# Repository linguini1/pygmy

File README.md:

# Pygmy

This project is a rocket flight computer design for my TRA L1 certification flight. The name is a play on the fact that
it's designed to be small and also runs on a Pi (Py) chip. Yes, that means you can program it with MicroPython (Py).

The Pygmy was designed with the [Apache NuttX RTOS][nuttx] in mind (you can find the board support for it
[here][pygmy-nx]), but it is also possible to program it using the Pico C SDK or MicroPython (or really, whatever else
you can flash on an RP2040).

<p align="center">
    
    <br/>
    Pygmy Rev B
</p>

<p align="center">
    
    <br/>
    The prototype board Pygmy Rev B with its ground station sibling, PygmyGS.
</p>

The flight computer also has a sibling ground station receiver, the PygmyGS. This board allows you to receive telemetry
from the ground and can interface with consumer hardware like a laptop through its USB-C serial interface.

<p align="center">
    
    <br/>
    The manufactured PygmyGS Rev A
</p>

<p align="center">
    
    <br/>
    Handheld for scale
</p>

<p align="center">
    
    <br/>
    The ECAD render of the PygmyGS Rev A
</p>

Here is the Pygmy within my L1 rocket:

## Motivation

I am a computer systems engineer who has designed avionics for my university's rocketry team for several years. I like
the challenge of designing, building and programming embedded systems for unique environments, like the inside of a
rocket. Although my L1 flight won't have the same challenges as my university's rockets (which fly up to 30k feet and
have hit Mach 1.89), it will still have challenges unique to rocketry like high vibration and lots of different forces,
arming requirements and logging speed requirements. Most differently, this flight computer is entirely my own project to
experiment with as I please!

My L1, as far as I'm concerned, is to be a relatively standard L1 rocket build (not a kit, still my own) outside of this
flight computer. That way I can get my cert while having a rocket which meets my primary goal: being a vessel for my
flight computer.

This flight computer, once flight tested in an L1, should in theory be capable up to L3 flights as a data logger.
Deployment control may be added in later revisions as I attempt my L2 certification with electronics, but that will be
much later.

## Usage

To learn how to use the Pygmy, please check the manual under the `docs/` sub-directory. This manual contains both the
user guide for operation and a detailed developer guide.

Both guides are currently under construction.

## Other Goodies

Along with the Pygmy and PygmyGS E-CAD design files _and_ free,
[open-source software](https://github.com/linguini1/pygmy-nx), there is additionally parametric CAD enclosure designs
included in this repository.

The PygmyGS case can be found under [`ground-station/enclosure`](./ground-station/enclosure), along with an assembly
file so you can see the PygmyGS mounted inside it with all the fasteners.

<p align="center">
    
    <br/>
    PygmyGS hinged enclosure
</p>

A sample avionics bay for the Pygmy flight computer can be found under
[`flight-computer/enclosure`](./flight-computer/enclosure), along with an assembly file so you can see the Pygmy mounted
in the bay with a battery and arming switch. This design is also fully parametric so you can modify it to the body tube
diameter of your rocket, different battery size, etc. This design is largely based off of the configuration I flew in my
L1 certification flight, so feel free to fully change it depending on your constraints and desires! It is by no way the
recommended configuration for the Pygmy, just one possible design.

<p align="center">
    
    <br/>
    Pygmy sample avionics bay
</p>

[pygmy-nx]: https://github.com/linguini1/pygmy-nx
[nuttx]: https://nuttx.apache.org/

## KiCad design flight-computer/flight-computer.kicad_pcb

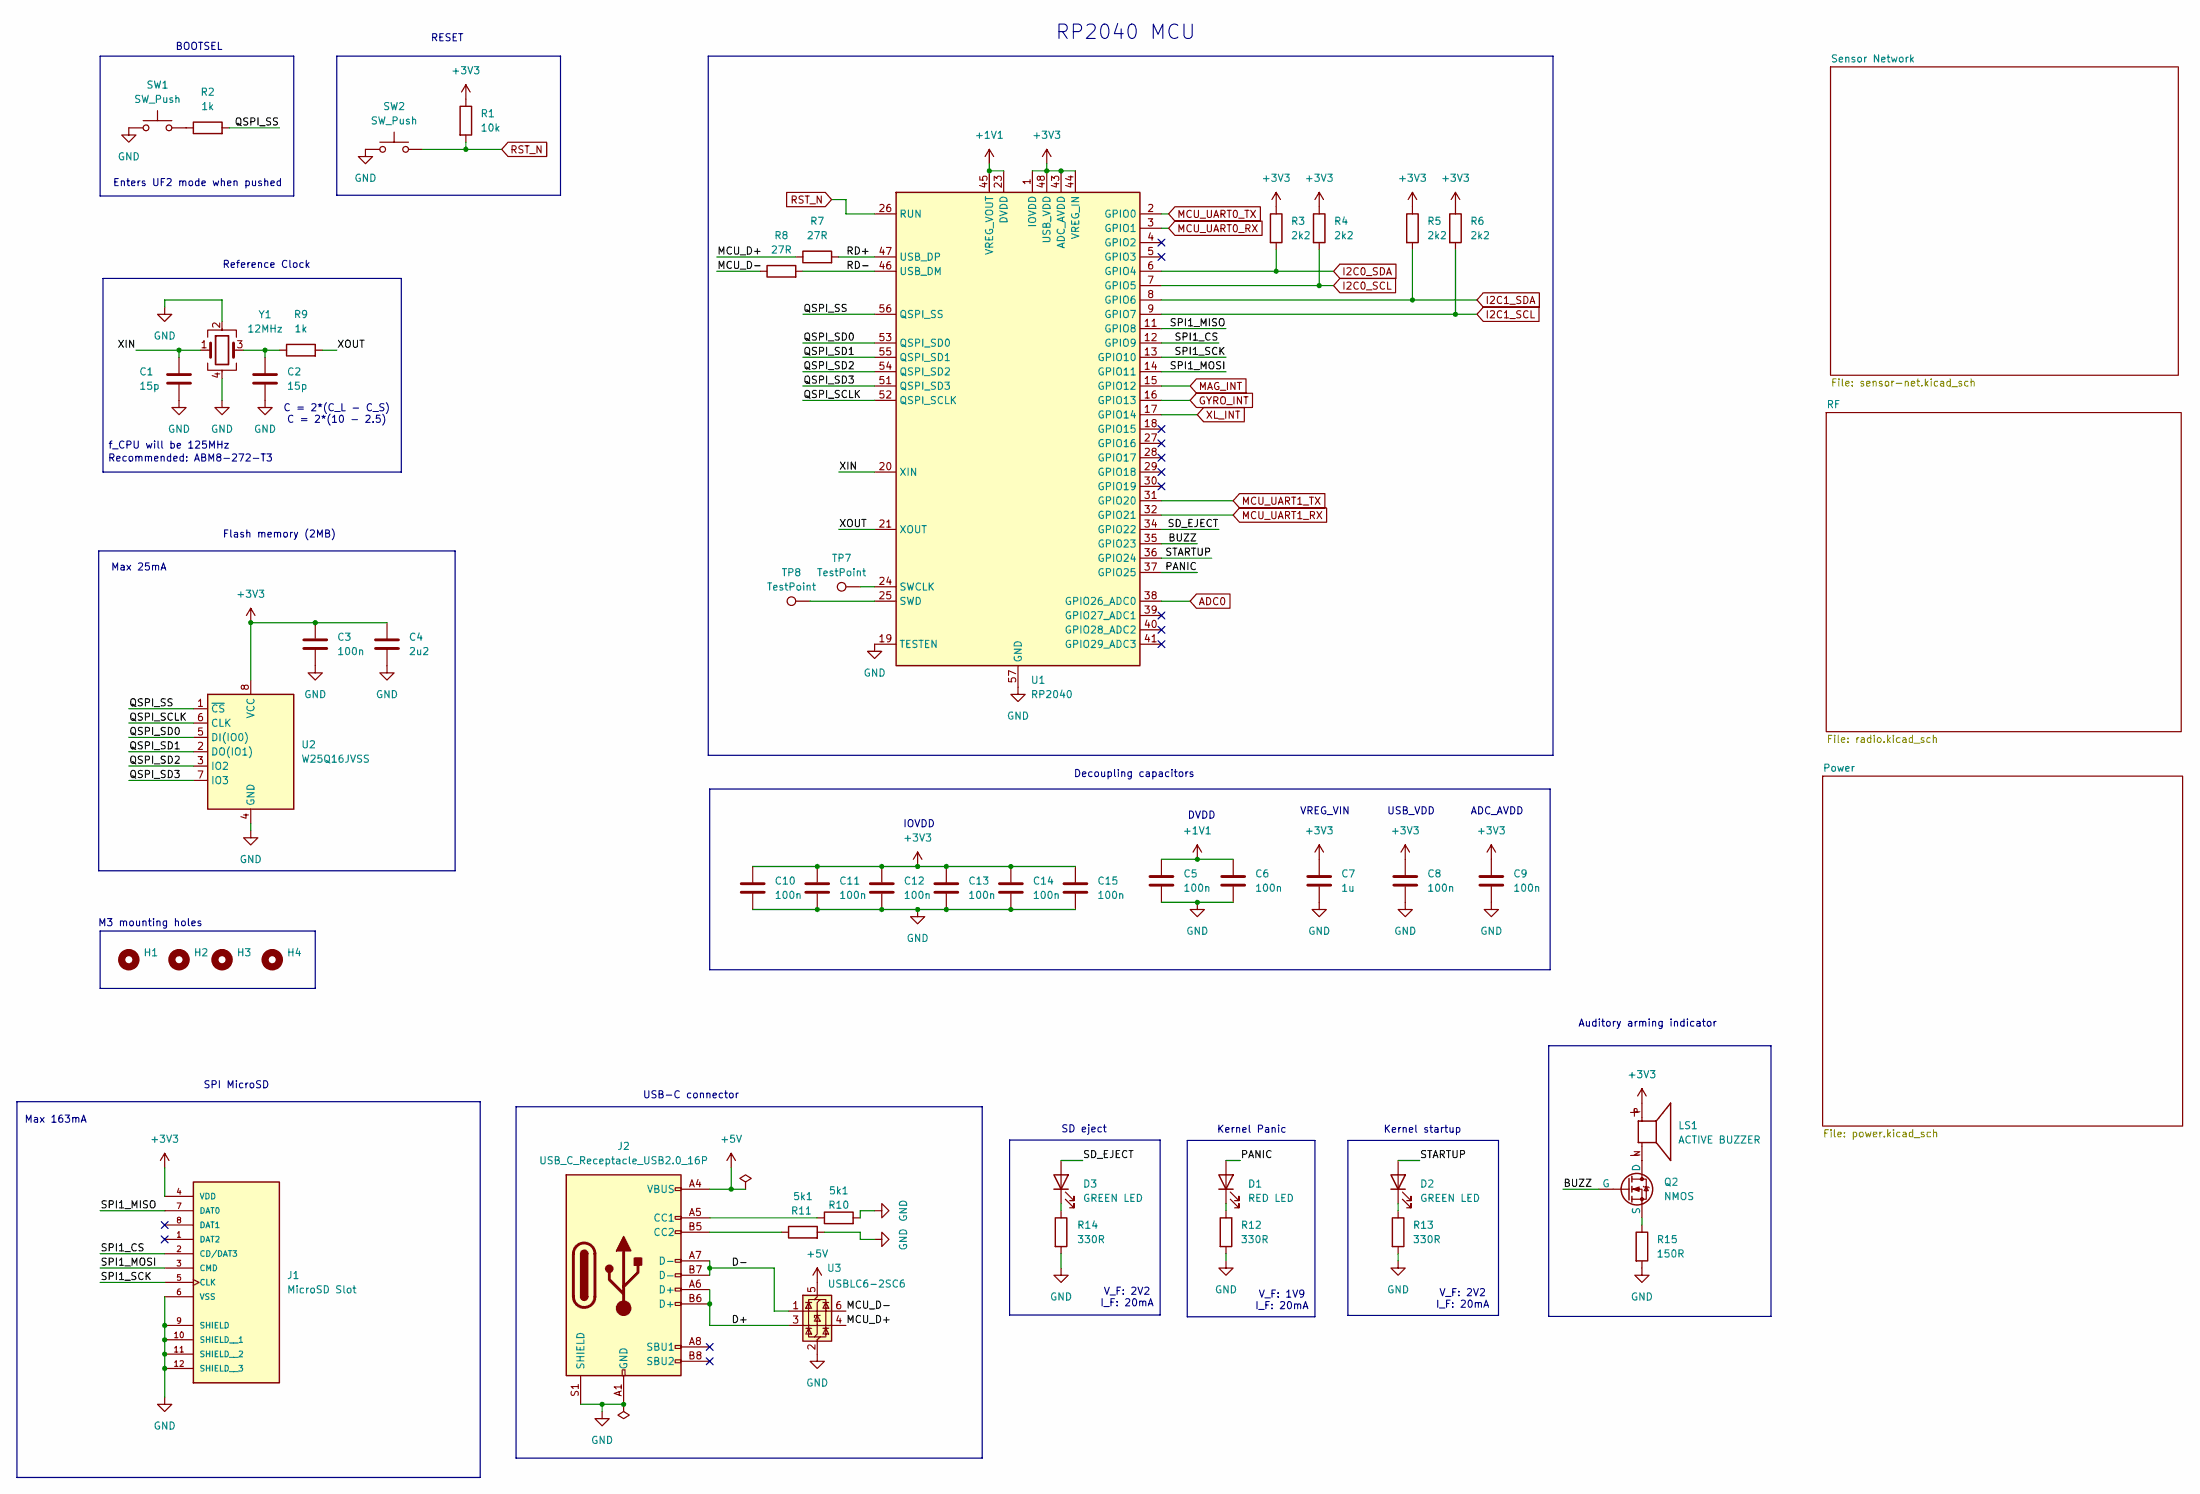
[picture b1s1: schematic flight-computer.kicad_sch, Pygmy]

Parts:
C1, C2: 15p; C_0402_1005Metric
C3, C5, C6, C8, C9, C10, C11, C12, C13, C14, C15: 100n; C_0402_1005Metric
C4: 2u2; C_0603_1608Metric
C7: 1u; C_0603_1608Metric
D1: RED LED; LED_0805_2012Metric
D2, D3: GREEN LED; LED_0805_2012Metric
H1, H2, H3, H4: MountingHole; MountingHole_3.2mm_M3
J1: MicroSD Slot; GCT_MEM2067-02-180-00-A_REVB
J2: USB_C_Receptacle_USB2.0_16P; USB_C_Receptacle_GCT_USB4105-xx-A_16P_TopMnt_Horizontal
LS1: ACTIVE BUZZER; XDCR_AI-1223-TWT-3V-2-R; PARTREV 3/18/2020
Q2: NMOS; SOT-23-3
R1: 10k; R_0402_1005Metric
R2, R9: 1k; R_0402_1005Metric
R3, R4, R5, R6: 2k2; R_0402_1005Metric
R7, R8: 27R; R_0402_1005Metric
R10, R11: 5k1; R_0402_1005Metric
R12, R13, R14: 330R; R_0402_1005Metric
R15: 150R; R_0402_1005Metric
SW1: SW_Push; SW_PUSH_6mm_H5mm
SW2: SW_Push; SolderJumper-2_P1.3mm_Open_TrianglePad1.0x1.5mm
TP7, TP8: TestPoint; TestPoint_Pad_D1.5mm
U1: RP2040; QFN-56-1EP_7x7mm_P0.4mm_EP3.2x3.2mm
U2: W25Q16JVSS; SOIC-8_5.23x5.23mm_P1.27mm
U3: USBLC6-2SC6; SOT-23-6
Y1: 12MHz; Crystal_SMD_3225-4Pin_3.2x2.5mm

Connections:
+1V1: C5.1, C6.1, U1.23 (DVDD), U1.45 (VREG_VOUT), U1.50 (DVDD)
+3V3: C3.1, C4.1, C7.1, C8.1, C9.1, C10.1, C11.1, C12.1, C13.1, C14.1, C15.1, J1.4 (VDD), LS1.P, R1.1, R3.1, R4.1, R5.1, R6.1, U1.1 (IOVDD), U1.10 (IOVDD), U1.22 (IOVDD), U1.33 (IOVDD), U1.42 (IOVDD), U1.43 (ADC_AVDD), U1.44 (VREG_IN), U1.48 (USB_VDD), U1.49 (IOVDD), U2.8 (VCC); also elsewhere on the board
+5V: J2.A4 (VBUS), J2.A9 (VBUS), J2.B4 (VBUS), J2.B9 (VBUS), U3.5 (VBUS); also elsewhere on the board
/BUZZ: Q2.1 (G), U1.35 (GPIO23)
/D+: J2.A6 (D+), J2.B6 (D+), U3.3 (I/O2)
/D-: J2.A7 (D-), J2.B7 (D-), U3.1 (I/O1)
/MCU_D+: R7.1, U3.4 (I/O2)
/MCU_D-: R8.1, U3.6 (I/O1)
/PANIC: D1.2 (A), U1.37 (GPIO25)
/QSPI_SCLK: U1.52 (QSPI_SCLK), U2.6 (CLK)
/QSPI_SD0: U1.53 (QSPI_SD0), U2.5 (DI(IO0))
/QSPI_SD1: U1.55 (QSPI_SD1), U2.2 (DO(IO1))
/QSPI_SD2: U1.54 (QSPI_SD2), U2.3 (IO2)
/QSPI_SD3: U1.51 (QSPI_SD3), U2.7 (IO3)
/QSPI_SS: R2.2, U1.56 (QSPI_SS), U2.1 (~CS)
/RD+: R7.2, U1.47 (USB_DP)
/RD-: R8.2, U1.46 (USB_DM)
/SD_EJECT: D3.2 (A), U1.34 (GPIO22)
/SPI1_CS: J1.2 (CD/DAT3), U1.12 (GPIO9)
/SPI1_MISO: J1.7 (DAT0), U1.11 (GPIO8)
/SPI1_MOSI: J1.3 (CMD), U1.14 (GPIO11)
/SPI1_SCK: J1.5 (CLK), U1.13 (GPIO10)
/STARTUP: D2.2 (A), U1.36 (GPIO24)
/XIN: C1.1, U1.20 (XIN), Y1.1
/XOUT: R9.2, U1.21 (XOUT)
ADC0: U1.38 (GPIO26_ADC0); also elsewhere on the board
GND: C1.2, C2.2, C3.2, C4.2, C5.2, C6.2, C7.2, C8.2, C9.2, C10.2, C11.2, C12.2, C13.2, C14.2, C15.2, J1.6 (VSS), J1.9 (SHIELD), J1.10 (SHIELD__1), J1.11 (SHIELD__2), J1.12 (SHIELD__3), J2.A1 (GND), J2.A12 (GND), J2.B1 (GND), J2.B12 (GND), J2.S1 (SHIELD), R10.2, R11.2, R12.2, R13.2, R14.2, R15.2, SW1.1, SW2.1, U1.19 (TESTEN), U1.57 (GND), U2.4 (GND), U3.2 (GND), Y1.2, Y1.4; also elsewhere on the board
GYRO_INT: U1.16 (GPIO13); also elsewhere on the board
I2C0_SCL: R4.2, U1.7 (GPIO5); also elsewhere on the board
I2C0_SDA: R3.2, U1.6 (GPIO4); also elsewhere on the board
I2C1_SCL: R6.2, U1.9 (GPIO7); also elsewhere on the board
I2C1_SDA: R5.2, U1.8 (GPIO6); also elsewhere on the board
MAG_INT: U1.15 (GPIO12); also elsewhere on the board
MCU_UART0_RX: U1.3 (GPIO1); also elsewhere on the board
MCU_UART0_TX: U1.2 (GPIO0); also elsewhere on the board
MCU_UART1_RX: U1.32 (GPIO21); also elsewhere on the board
MCU_UART1_TX: U1.31 (GPIO20); also elsewhere on the board
unnamed: C2.1, R9.1, Y1.3
unnamed: D1.1 (K), R12.1
unnamed: D2.1 (K), R13.1
unnamed: D3.1 (K), R14.1
unnamed: J2.A5 (CC1), R10.1
unnamed: J2.B5 (CC2), R11.1
unnamed: LS1.N, Q2.3 (D)
unnamed: Q2.2 (S), R15.1
unnamed: R2.1, SW1.2
unnamed 54: TP7.1, U1.24 (SWCLK); also elsewhere on the board
unnamed 55: TP8.1, U1.25 (SWD); also elsewhere on the board
RST_N: R1.2, SW2.2, U1.26 (RUN); also elsewhere on the board
XL_INT: U1.17 (GPIO14); also elsewhere on the board

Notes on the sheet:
Auditory arming indicator
RP2040 MCU
C = 2*(C_L - C_S) C = 2*(10 - 2.5)
Kernel Panic
Kernel startup
V_F: 2V2 I_F: 20mA
VREG_VIN
USB_VDD
Recommended: ABM8-272-T3
Max 163mA
DVDD
M3 mounting holes
IOVDD
SPI MicroSD
USB-C connector
f_CPU will be 125MHz
V_F: 1V9 I_F: 20mA
Decoupling capacitors
BOOTSEL
Reference Clock
ADC_AVDD
RESET
Flash memory (2MB)
Max 25mA
Enters UF2 mode when pushed
SD eject

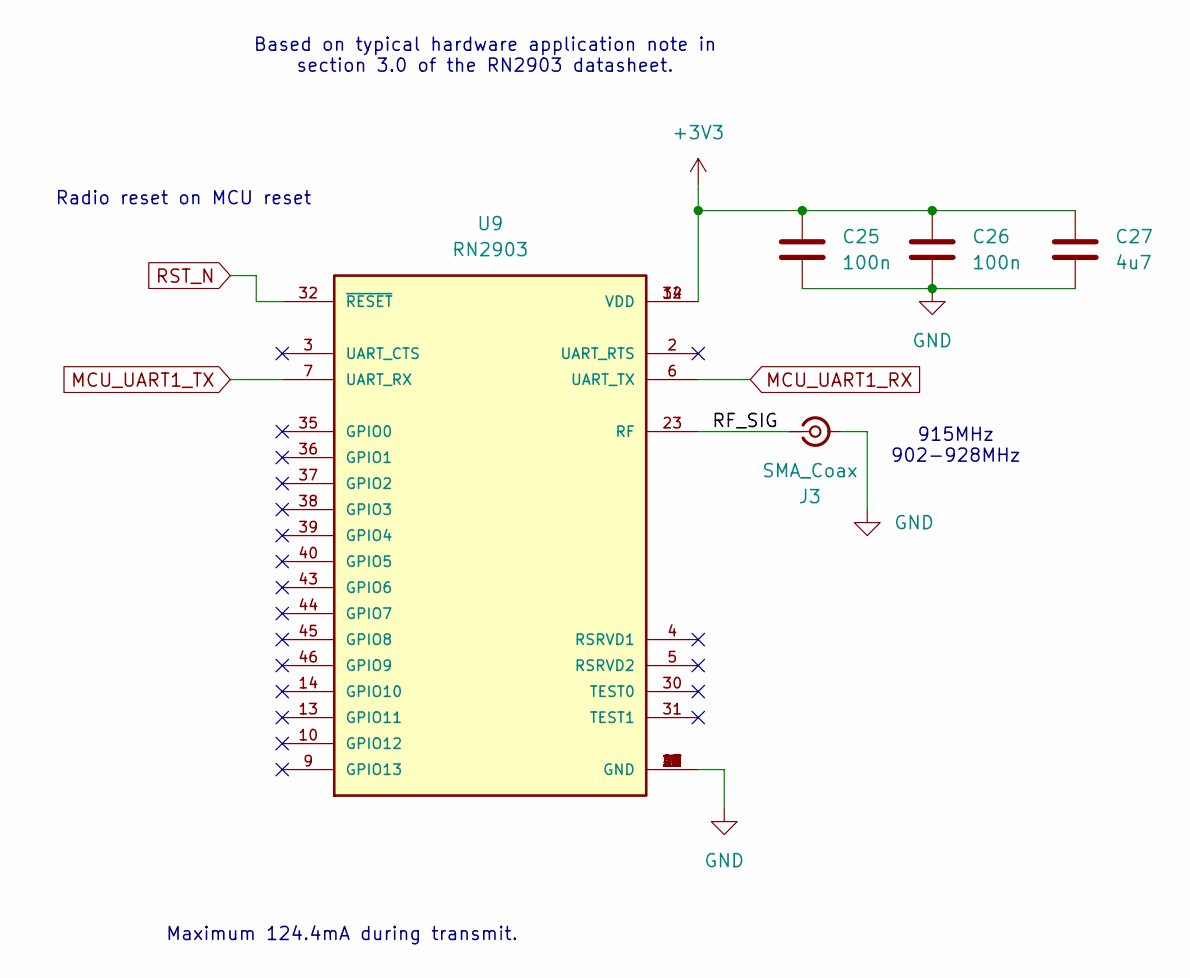
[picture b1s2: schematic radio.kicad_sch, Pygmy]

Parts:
C25, C26: 100n; C_0402_1005Metric
C27: 4u7; C_0603_1608Metric
J3: SMA_Coax; SMA_Molex_73251-1153_EdgeMount_Horizontal
U9: RN2903

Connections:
+3V3: C25.1, C26.1, C27.1, U9.12 (VDD), U9.34 (VDD); also elsewhere on the board
/RF/RF_SIG: J3.1 (In), U9.23 (RF)
GND: C25.2, C26.2, C27.2, J3.2 (Ext), U9.1 (GND), U9.8 (GND), U9.11 (GND), U9.20 (GND), U9.21 (GND), U9.22 (GND), U9.24 (GND), U9.26 (GND), U9.27 (GND), U9.28 (GND), U9.33 (GND), U9.41 (GND), U9.47 (GND); also elsewhere on the board
MCU_UART1_RX: U9.6 (UART_TX); also elsewhere on the board
MCU_UART1_TX: U9.7 (UART_RX); also elsewhere on the board
RST_N: U9.32 (~RESET); also elsewhere on the board

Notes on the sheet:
915MHz 902-928MHz
Radio reset on MCU reset
Maximum 124.4mA during transmit.
Based on typical hardware application note in section 3.0 of the RN2903 datasheet.

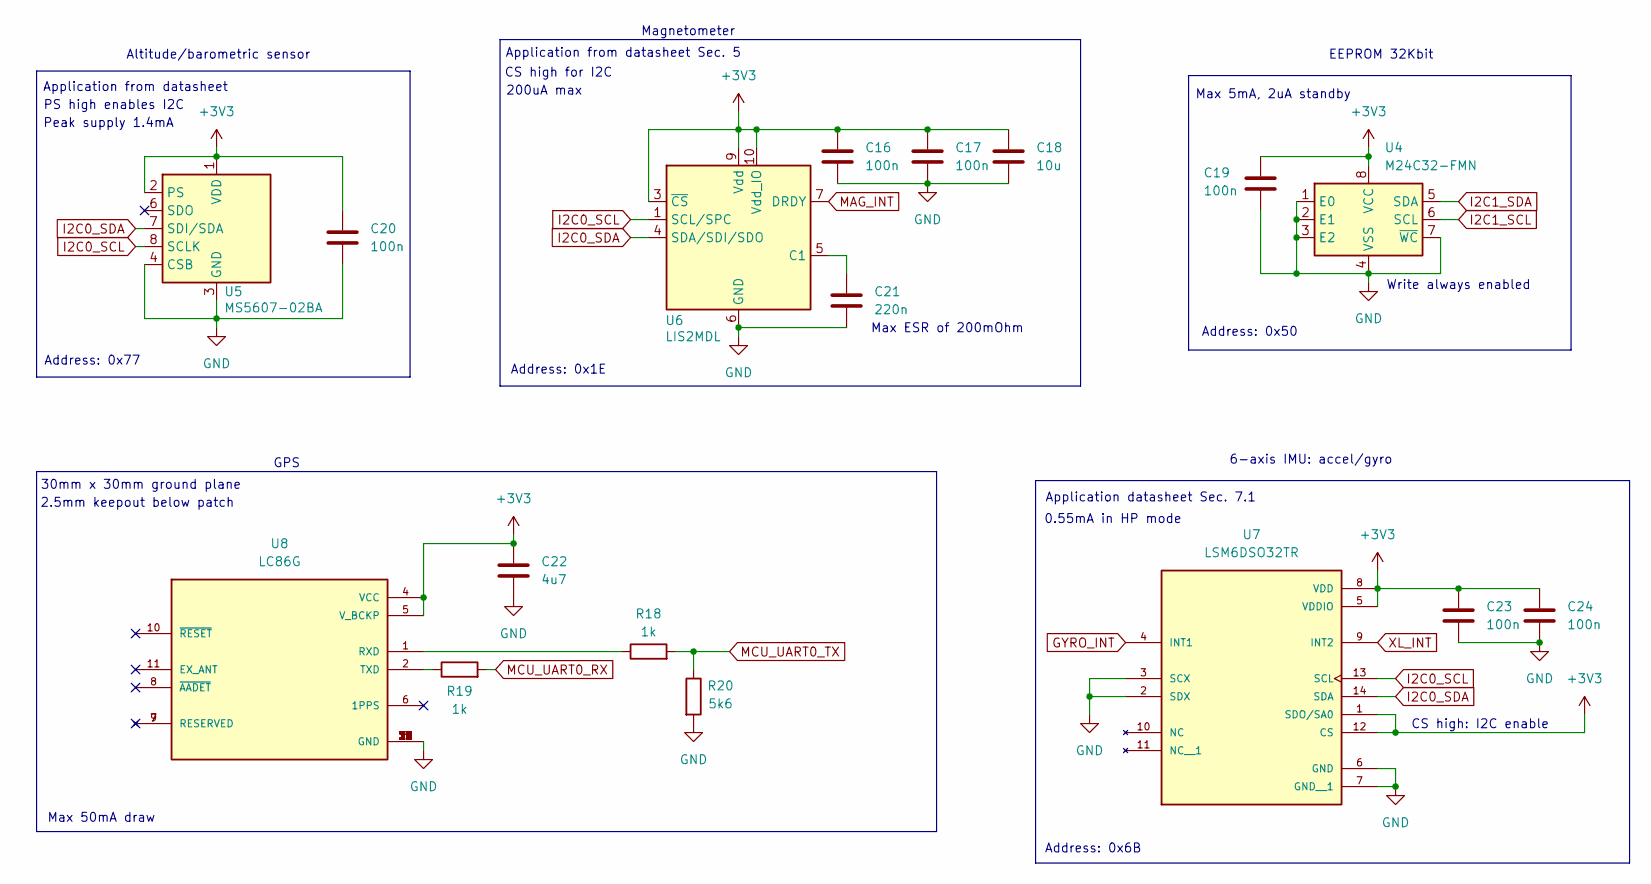
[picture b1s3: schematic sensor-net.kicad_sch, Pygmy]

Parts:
C16, C17, C19, C20, C23, C24: 100n; C_0402_1005Metric
C18: 10u; C_0603_1608Metric
C21: 220n; C_0603_1608Metric
C22: 4u7; C_0603_1608Metric
R18, R19: 1k; R_0402_1005Metric
R20: 5k6; R_0402_1005Metric
U4: M24C32-FMN; SOIC-8_3.9x4.9mm_P1.27mm
U5: MS5607-02BA; LGA-8_3x5mm_P1.25mm
U6: LIS2MDL; LGA-12_2x2mm_P0.5mm
U7: LSM6DSO32TR; XDCR_LSM6DSO32TR
U8: LC86G; XCVR_LC86G

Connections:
+3V3: C16.1, C17.1, C18.1, C19.1, C20.1, C22.1, C23.1, C24.1, U4.8 (VCC), U5.1 (VDD), U5.2 (PS), U6.3 (~CS), U6.9 (Vdd), U6.10 (Vdd_IO), U7.1 (SDO/SA0), U7.5 (VDDIO), U7.8 (VDD), U7.12 (CS), U8.4 (VCC), U8.5 (V_BCKP); also elsewhere on the board
GND: C16.2, C17.2, C18.2, C19.2, C20.2, C21.2, C22.2, C23.2, C24.2, R20.2, U4.1 (E0), U4.2 (E1), U4.3 (E2), U4.4 (VSS), U4.7 (~WC), U5.3 (GND), U5.4 (CSB), U5.5 (CSB), U6.6 (GND), U6.8 (GND), U7.2 (SDX), U7.3 (SCX), U7.6 (GND), U7.7 (GND__1), U8.3 (GND), U8.12 (GND), U8.13 (GND), U8.14 (GND), U8.15 (GND), U8.16 (GND), U8.17 (GND), U8.18 (GND), U8.19 (GND), U8.20 (GND), U8.21 (GND), U8.22 (GND), U8.23 (GND), U8.24 (GND), U8.25 (GND), U8.26 (GND), U8.27 (GND), U8.28 (GND), U8.29 (GND), U8.30 (GND), U8.31 (GND), U8.32 (GND), U8.33 (GND), U8.34 (GND), U8.35 (GND), U8.36 (GND); also elsewhere on the board
GYRO_INT: U7.4 (INT1); also elsewhere on the board
I2C0_SCL: U5.8 (SCLK), U6.1 (SCL/SPC), U7.13 (SCL); also elsewhere on the board
I2C0_SDA: U5.7 (SDI/SDA), U6.4 (SDA/SDI/SDO), U7.14 (SDA); also elsewhere on the board
I2C1_SCL: U4.6 (SCL); also elsewhere on the board
I2C1_SDA: U4.5 (SDA); also elsewhere on the board
MAG_INT: U6.7 (DRDY); also elsewhere on the board
MCU_UART0_RX: R19.2; also elsewhere on the board
MCU_UART0_TX: R18.2, R20.1; also elsewhere on the board
unnamed: C21.1, U6.5 (C1)
unnamed: R18.1, U8.1 (RXD)
unnamed: R19.1, U8.2 (TXD)
XL_INT: U7.9 (INT2); also elsewhere on the board

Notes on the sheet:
Application datasheet Sec. 7.1
CS high for I2C
Address: 0x50
Address: 0x6B
Application from datasheet Sec. 5
Address: 0x77
30mm x 30mm ground plane
Altitude/barometric sensor
Max 5mA, 2uA standby
GPS
6-axis IMU: accel/gyro
200uA max
Magnetometer
Address: 0x1E
EEPROM 32Kbit
CS high: I2C enable
Write always enabled
PS high enables I2C
Application from datasheet
Peak supply 1.4mA
2.5mm keepout below patch
Max 50mA draw
0.55mA in HP mode
Max ESR of 200mOhm

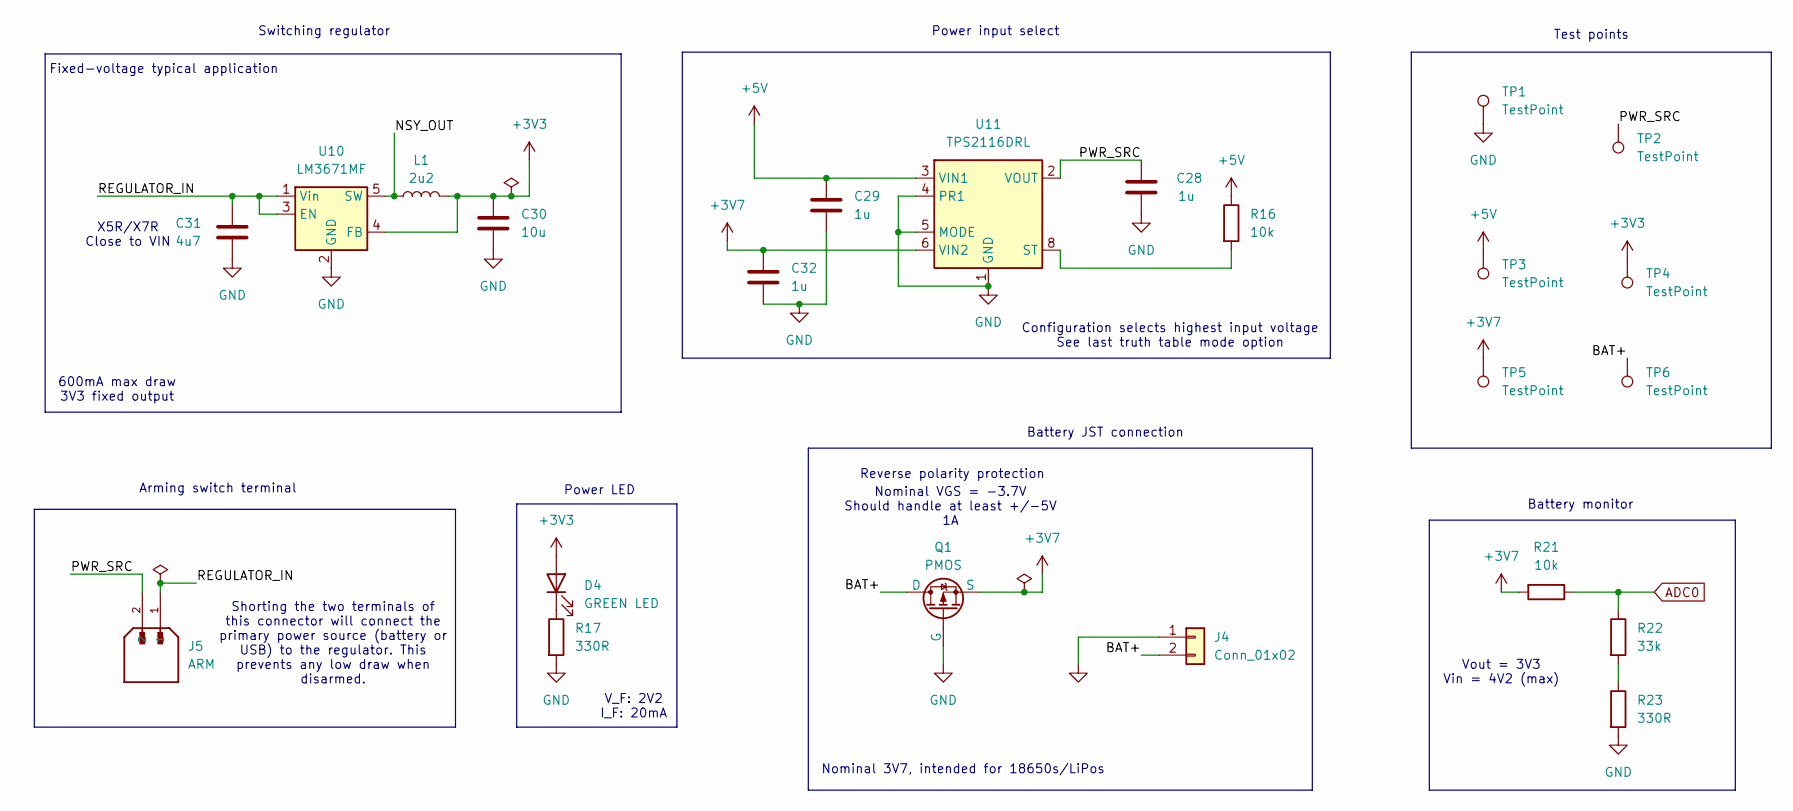
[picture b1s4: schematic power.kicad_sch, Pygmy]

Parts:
C28, C29, C32: 1u; C_0603_1608Metric
C30: 10u; C_0603_1608Metric
C31: 4u7; C_0603_1608Metric
D4: GREEN LED; LED_0805_2012Metric
J4: Conn_01x02; JST_PH_S2B-PH-K_1x02_P2.00mm_Horizontal
J5: ARM; TerminalBlock_Phoenix_MPT-0,5-2-2.54_1x02_P2.54mm_Horizontal; PARTREV A2
L1: 2u2; LPO3310222MLC
Q1: PMOS; SOT-23-3
R16, R21: 10k; R_0402_1005Metric
R17, R23: 330R; R_0402_1005Metric
R22: 33k; R_0402_1005Metric
TP1, TP2, TP4, TP5, TP6: TestPoint; TestPoint_Pad_D1.5mm
TP3: TestPoint; TestPoint_Pad_D1.0mm
U10: LM3671MF; TSOT-23-5
U11: TPS2116DRL; SOT-583-8

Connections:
+3V3: C30.1, D4.2 (A), L1.2, TP4.1, U10.4 (FB); also elsewhere on the board
+3V7: C32.1, Q1.2 (S), R21.2, TP5.1, U11.6 (VIN2); also elsewhere on the board
+5V: C29.1, R16.1, TP3.1, U11.3 (VIN1); also elsewhere on the board
/Power/BAT+: J4.2, Q1.3 (D), TP6.1; also elsewhere on the board
/Power/NSY_OUT: L1.1, U10.5 (SW)
/Power/PWR_SRC: C28.1, J5.2, TP2.1, U11.2 (VOUT), U11.7 (VOUT); also elsewhere on the board
/Power/REGULATOR_IN: C31.1, J5.1, U10.1 (Vin), U10.3 (EN)
ADC0: R21.1, R22.1; also elsewhere on the board
GND: C28.2, C29.2, C30.2, C31.2, C32.2, J4.1, Q1.1 (G), R17.2, R23.2, TP1.1, U10.2 (GND), U11.1 (GND), U11.4 (PR1), U11.5 (MODE); also elsewhere on the board
unnamed: D4.1 (K), R17.1
unnamed: R22.2, R23.1
unnamed: R16.2, U11.8 (ST)

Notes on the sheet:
Arming switch terminal
V_F: 2V2 I_F: 20mA
Switching regulator
Nominal VGS = -3.7V Should handle at least +/-5V 1A
Configuration selects highest input voltage See last truth table mode option
Vout = 3V3 Vin = 4V2 (max)
Shorting the two terminals of this connector will connect the primary power source (battery or USB) to the regulator. This prevents any low draw when disarmed.
600mA max draw 3V3 fixed output
Nominal 3V7, intended for 18650s/LiPos
Fixed-voltage typical application
Test points
Power input select
X5R/X7R Close to VIN
Battery JST connection
Power LED
Reverse polarity protection
Battery monitor

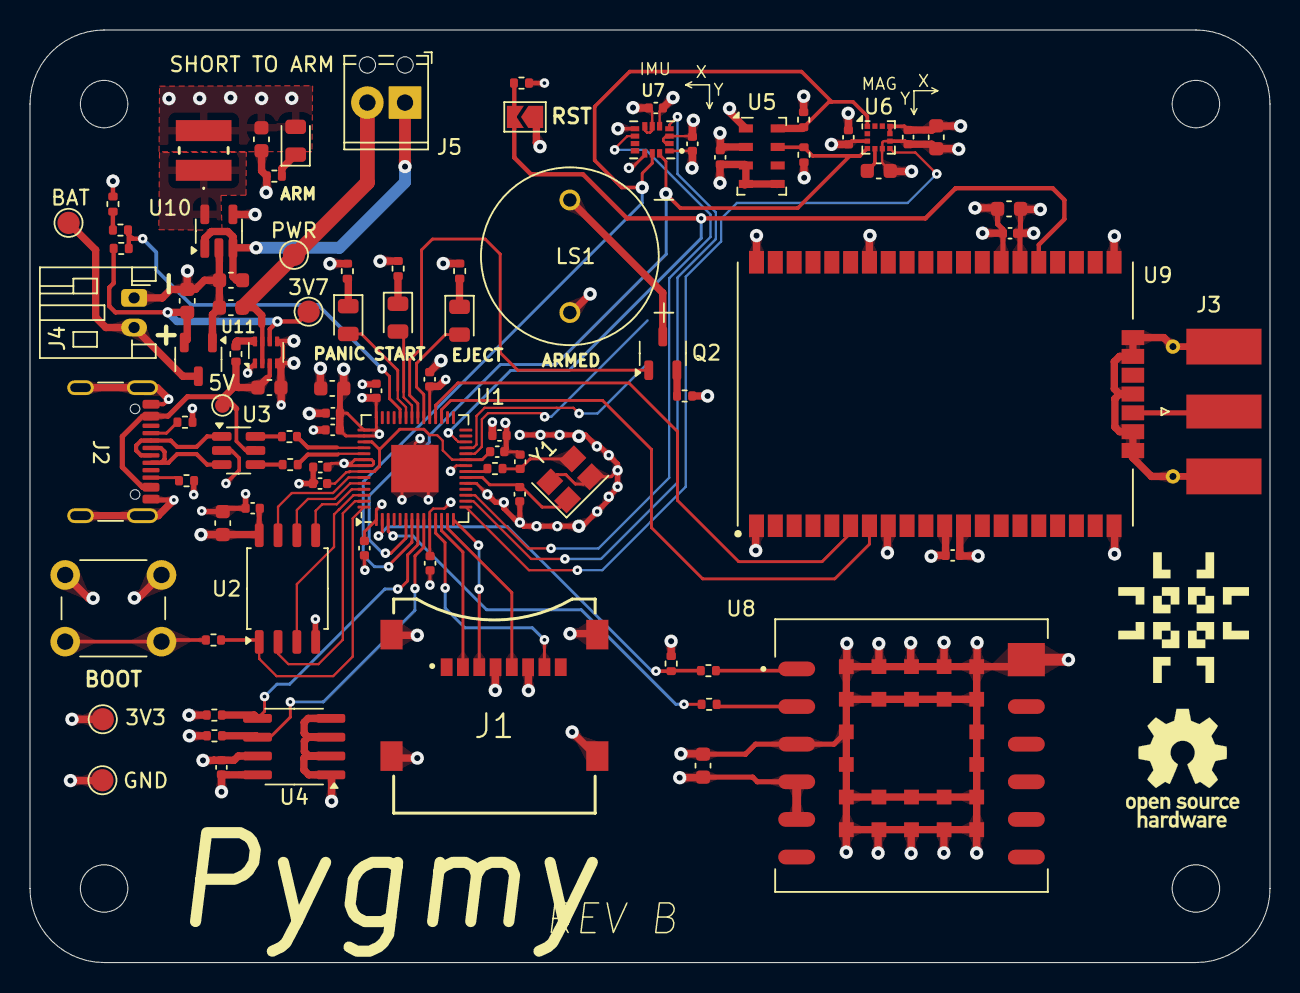
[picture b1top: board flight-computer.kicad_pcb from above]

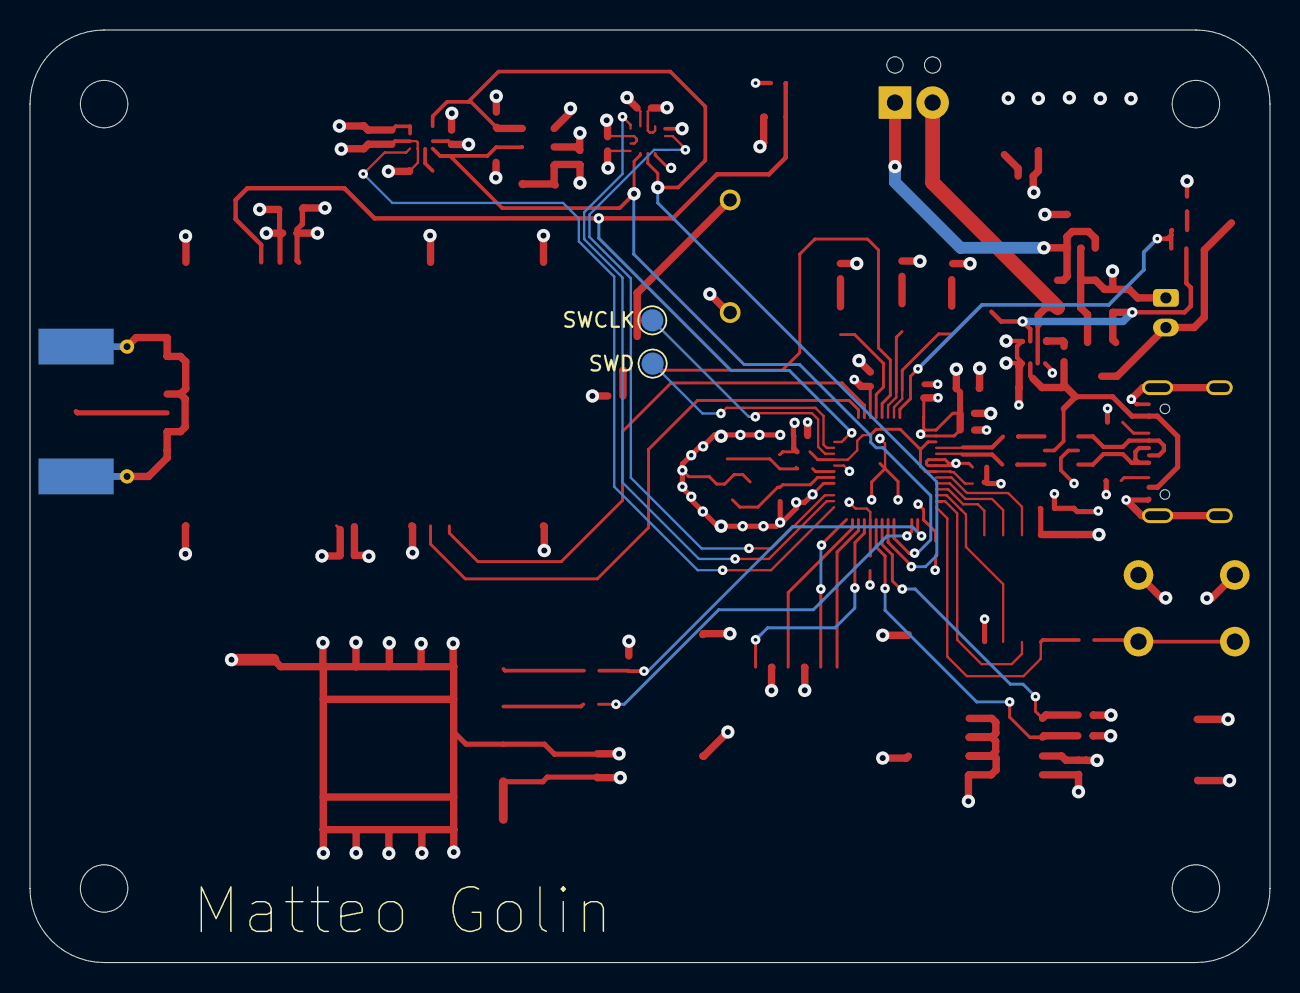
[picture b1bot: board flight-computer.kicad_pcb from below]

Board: 4 copper layers, 83.7 x 62.9 mm, 94 parts (2 on the bottom side), 62 nets.

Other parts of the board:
3V3, 3V7: TestPoint; TestPoint_Pad_D1.5mm
5V: TestPoint; TestPoint_Pad_D1.0mm
BAT: TestPoint; TestPoint_Pad_D1.5mm
GND: TestPoint; TestPoint_Pad_D1.5mm
PWR: TestPoint; TestPoint_Pad_D1.5mm
SWCLK: TestPoint; TestPoint_Pad_D1.5mm
SWD: TestPoint; TestPoint_Pad_D1.5mm

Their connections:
+3V3: 3V3.1; also elsewhere on the board
+3V7: 3V7.1; also elsewhere on the board
+5V: 5V.1; also elsewhere on the board
/Power/BAT+: BAT.1; also elsewhere on the board
/Power/PWR_SRC: PWR.1; also elsewhere on the board
GND: GND.1; also elsewhere on the board
unnamed 54: SWCLK.1; also elsewhere on the board
unnamed 55: SWD.1; also elsewhere on the board

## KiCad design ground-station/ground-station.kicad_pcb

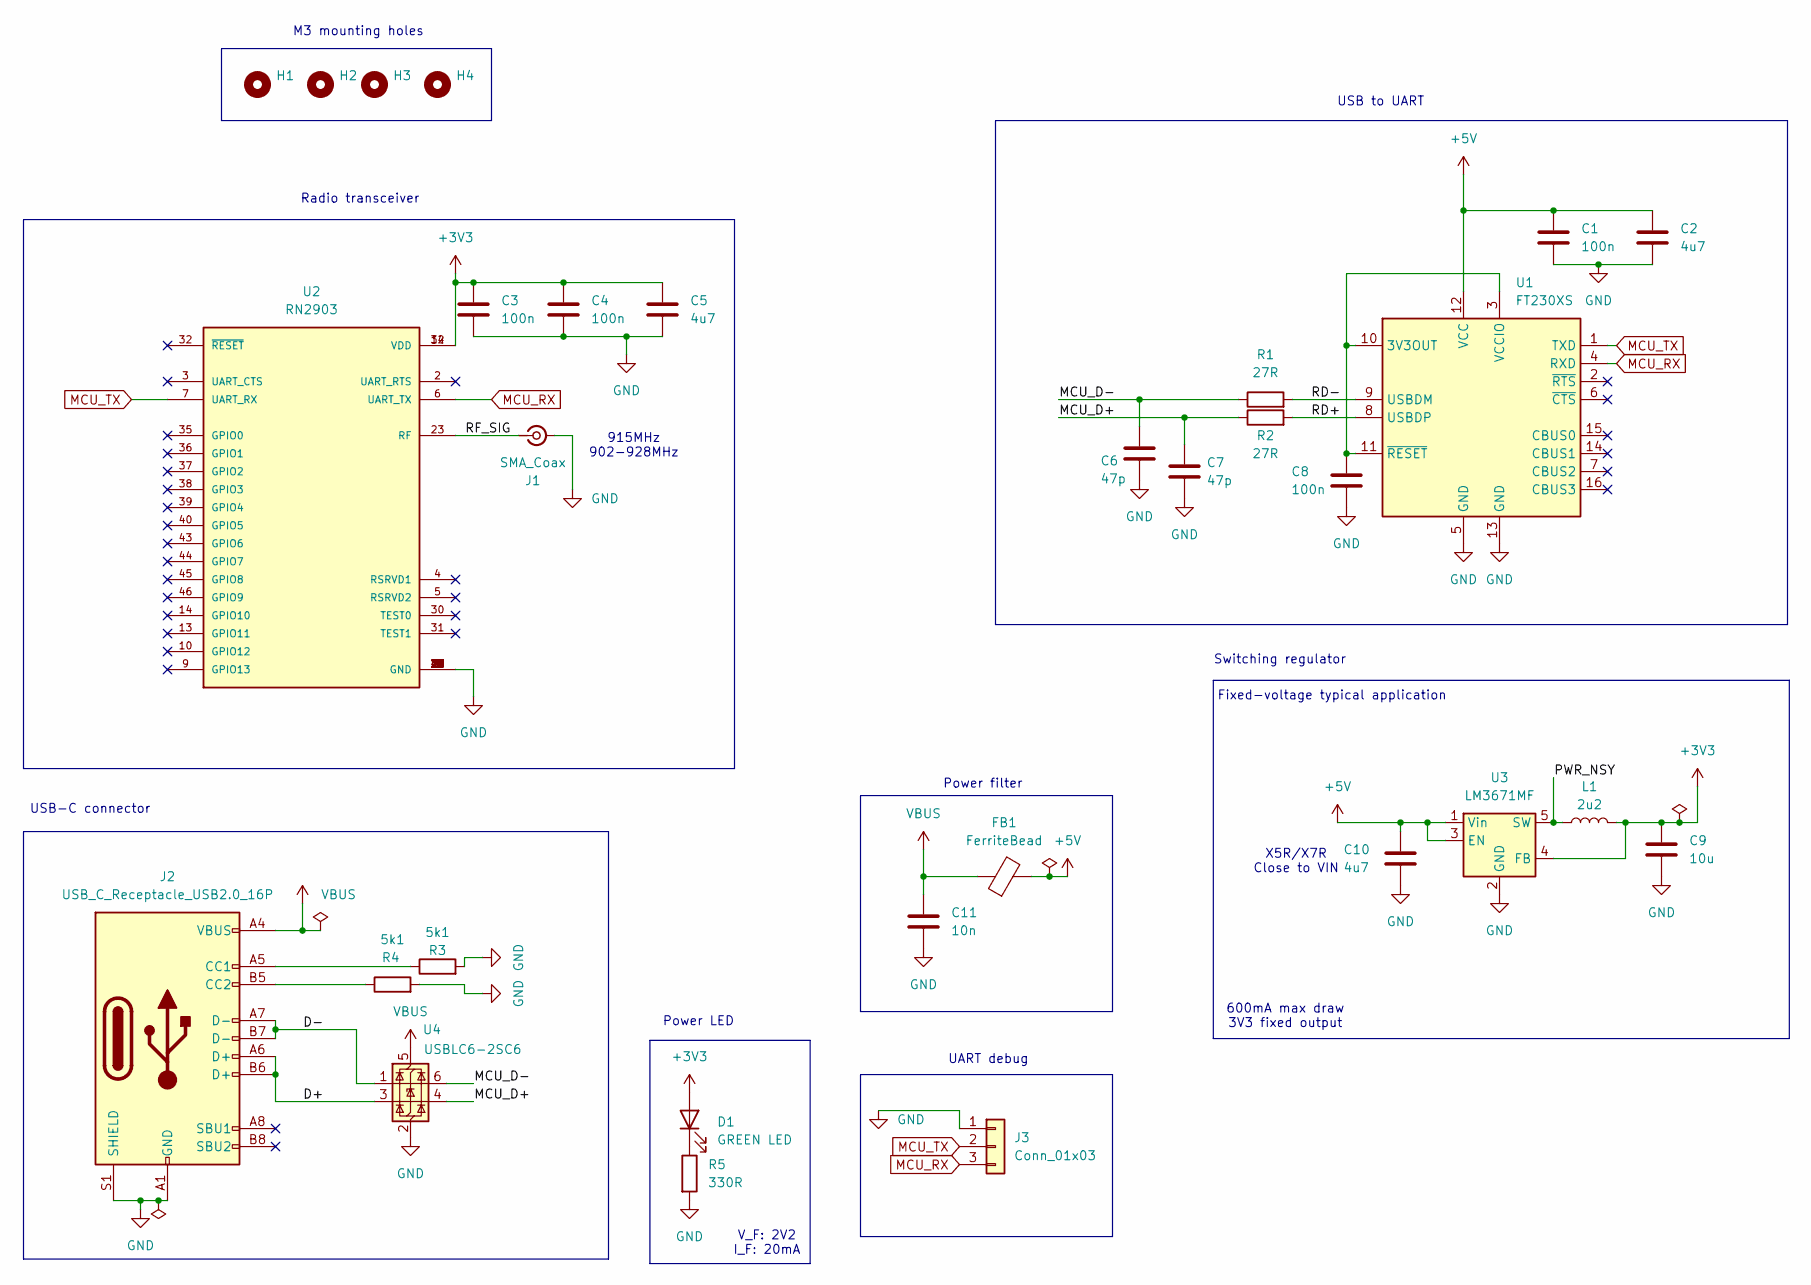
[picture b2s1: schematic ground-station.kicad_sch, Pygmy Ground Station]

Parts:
C1, C3, C4, C8: 100n; C_0402_1005Metric
C2, C5, C10: 4u7; C_0603_1608Metric
C6, C7: 47p; C_0402_1005Metric
C9: 10u; C_0603_1608Metric
C11: 10n; C_0402_1005Metric
D1: GREEN LED; LED_0805_2012Metric
FB1: FerriteBead; L_0805_2012Metric
H1, H2, H3, H4: MountingHole; MountingHole_3.2mm_M3
J1: SMA_Coax; SMA_Molex_73251-1153_EdgeMount_Horizontal
J2: USB_C_Receptacle_USB2.0_16P; USB_C_Receptacle_GCT_USB4105-xx-A_16P_TopMnt_Horizontal
J3: Conn_01x03; PinHeader_1x03_P2.54mm_Vertical
L1: 2u2; LPO3310222MLC
R1, R2: 27R; R_0402_1005Metric
R3, R4: 5k1; R_0402_1005Metric
R5: 330R; R_0402_1005Metric
U1: FT230XS; SSOP-16_3.9x4.9mm_P0.635mm
U2: RN2903
U3: LM3671MF; TSOT-23-5
U4: USBLC6-2SC6; SOT-23-6

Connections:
+3V3: C3.1, C4.1, C5.1, C9.1, D1.2 (A), L1.2, U2.12 (VDD), U2.34 (VDD), U3.4 (FB)
+5V: C1.1, C2.1, C10.1, FB1.2, U1.12 (VCC), U3.1 (Vin), U3.3 (EN)
/D+: J2.A6 (D+), J2.B6 (D+), U4.3 (I/O2)
/D-: J2.A7 (D-), J2.B7 (D-), U4.1 (I/O1)
/MCU_D+: C7.1, R2.1, U4.4 (I/O2)
/MCU_D-: C6.1, R1.1, U4.6 (I/O1)
/PWR_NSY: L1.1, U3.5 (SW)
/RD+: R2.2, U1.8 (USBDP)
/RD-: R1.2, U1.9 (USBDM)
/RF_SIG: J1.1 (In), U2.23 (RF)
GND: C1.2, C2.2, C3.2, C4.2, C5.2, C6.2, C7.2, C8.2, C9.2, C10.2, C11.2, J1.2 (Ext), J2.A1 (GND), J2.A12 (GND), J2.B1 (GND), J2.B12 (GND), J2.S1 (SHIELD), J3.1, R3.2, R4.2, R5.2, U1.5 (GND), U1.13 (GND), U2.1 (GND), U2.8 (GND), U2.11 (GND), U2.20 (GND), U2.21 (GND), U2.22 (GND), U2.24 (GND), U2.26 (GND), U2.27 (GND), U2.28 (GND), U2.33 (GND), U2.41 (GND), U2.47 (GND), U3.2 (GND), U4.2 (GND)
MCU_RX: J3.3, U1.4 (RXD), U2.6 (UART_TX)
MCU_TX: J3.2, U1.1 (TXD), U2.7 (UART_RX)
unnamed: D1.1 (K), R5.1
unnamed: J2.A5 (CC1), R3.1
unnamed: J2.B5 (CC2), R4.1
unnamed: C8.1, U1.3 (VCCIO), U1.10 (3V3OUT), U1.11 (~RESET)
VBUS: C11.1, FB1.1, J2.A4 (VBUS), J2.A9 (VBUS), J2.B4 (VBUS), J2.B9 (VBUS), U4.5 (VBUS)

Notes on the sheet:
V_F: 2V2 I_F: 20mA
UART debug
Switching regulator
Fixed-voltage typical application
USB-C connector
Power LED
Power filter
M3 mounting holes
Radio transceiver
600mA max draw 3V3 fixed output
X5R/X7R Close to VIN
915MHz 902-928MHz
USB to UART

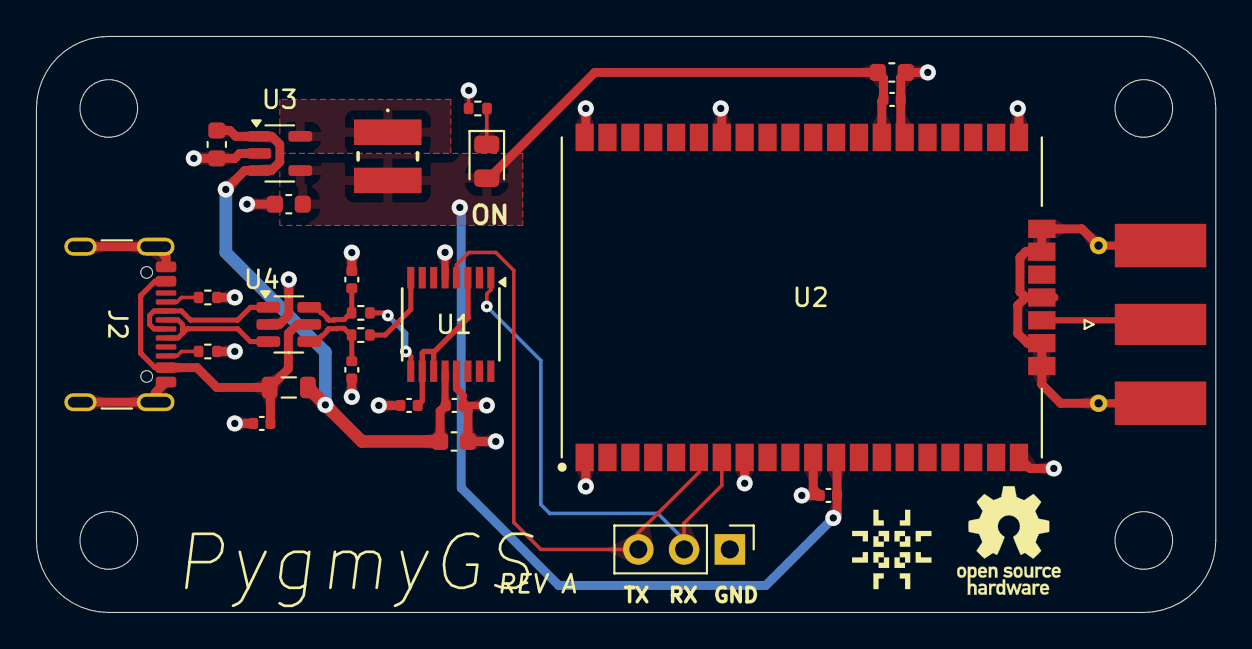
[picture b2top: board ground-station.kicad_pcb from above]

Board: 4 copper layers, 65.5 x 32.0 mm, 30 parts (0 on the bottom side), 18 nets.

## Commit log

2024-11-11 Initial commit.
2024-11-13 Added power circuitry and status LEDs. Went for an LDO with very low dropout voltage to reduce potential noise from a switching reg.
2024-11-13 Duplicate project removed
2024-11-13 Add title block
2024-11-21 Added decoupling caps to RN2483 and fixed antenna connection. Also settled on easy GPS.
2024-11-21 Updated power supply to use buck regulator and power input MUX. Also computed current draw of the board to size power regulator.
2024-11-21 Added capacitors to MUX to supply transient power when switching.
2024-11-21 Added footprints for all components
2024-11-21 Updated PCB so components are now on there.
2024-11-27 Remove unnecessary footprints.
2024-11-27 Update radio module to RN2903 for unlicensed band.
2024-11-27 Update net names.
2024-11-27 Moved around files to make a new documents folder.
2024-11-27 Added current draw to the manual.
2024-11-27 Filled out the BOM for the schematic. Consolidated some components and changed footprint sizes.
2024-11-27 Updated inductor footprint.
2024-11-27 Initial layout
2024-12-27 Updated GPS to L86G
2024-12-27 Added mounting holes and copper pours.
2024-12-28 Added reverse polarity protection on JST connector
2024-12-28 Almost done routing
2024-12-28 Added test points and finished routing
2024-12-28 Add image to README
2024-12-28 Teardrops and some cleanup
2024-12-28 Fixed disconnected 1V1 rails
2024-12-30 Added battery charge monitor
2024-12-30 Added interrupt lines for IMU and magnetometer
2024-12-30 Battery charge detection after reverse polarity protection for safety.
2024-12-31 Revamping docs, added SWD test pads.
2024-12-31 Changed LED resistors to 330 ohms to reduce brightness.
2024-12-31 Added MOSFET to drive the buzzer.
2024-12-31 Updated documentation to be split into user manual and developer manual
2025-01-01 Added keepout for patch antenna
2025-01-01 Updated keepout to not keepout footprints to resolve DRC error becuase it was under the GPS
2025-01-01 Made terminal block smaller.
2025-01-02 Removed some items from the paste layers, namely the SMA connector and USB throughole portions.
2025-01-02 Drill files made.
2025-01-02 Starting ground station design.
2025-01-02 Ignore gerber files
2025-01-02 Removed DRC errors on schematic by adding power flags.
2025-01-02 Created initial PCB layout for ground station.
2025-01-02 Modified paste layer
2025-01-02 Routing finished for ground station.
2025-01-02 Renamed directory to flight computer to differentiate from ground station
2025-01-02 Generated all gerbers for manufacture.
2025-01-02 Update README with better motivation and ground station image.
2025-01-02 BOMS exported and sorted.
2025-01-02 Add image of ground station
2025-01-02 Update image of Pygmy to final version
2025-01-03 Update silkscreen to show reset pins.
2025-01-03 Final render.
2025-01-03 Teardrop ground station.
2025-01-03 Remove out of stock LED from BOMS
2025-01-04 Ground station enclosure prototype complete
2025-01-08 Added step files necessary for enclosure assembly
2025-01-08 Start of enclosure
2025-01-08 Added hinges.
2025-01-08 Bottom of the case has finished shape.
2025-01-08 Added holes for inserts
2025-01-08 Added rough holes for SMA and USBC
2025-01-08 Created initial assembly to verify fits.
2025-01-08 Added lid
2025-01-09 Started replication of avionics bay in FreeCAD for others.
2025-01-09 Added flight computer on standoffs
2025-01-09 Sleds are now part of the assembly
2025-01-09 Added rails and sled screws
2025-01-09 Added hex nuts
2025-01-09 Fixed battery case holes
2025-01-09 Fix Pygmy rotation
2025-01-09 Added back hinges to lid.
2025-01-09 Groove mate is complete
2025-01-09 Added images of the enclosures.
2025-01-09 Added front hinges to the enclosure and re-rendered
2025-01-10 Added READMEs for enclosures and attribution to some inspirational resources.
2025-01-10 Added TODO list
2025-01-10 Added image of L1 assembly
2025-01-11 Add images of the manufactured board
2025-01-12 Updated to REV-B; KiCAD's default footprint (or at least first appearing) for the SMD crystal didn't match the datasheet and I didn't catch that. This was the only thing preventing me from booting an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
2025-01-12 Added silkscreen for magnetometer
2025-01-12 Resolved all DRC issues.
2025-01-12 Ordered part 2
2025-01-12 Added buffer area for the antenna connector and USB-C connector so it is possible to attach the antenna and cable
2025-01-12 Heat set inserts now cut into the base more.
2025-01-23 Update to Pygmy Rev B
2025-01-24 Add NuttX support link
2025-01-24 Fix link
2025-03-23 Updated USB slot to be wider.
2025-07-08 Fix link formatting
